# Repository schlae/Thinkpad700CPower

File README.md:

# Thinkpad 700C Power Supply Board

I've reverse engineered the power board from a Thinkpad 700C. The P/N is 35G4785, and the FRU number is 48G3712. A very similar or identical board is also present in the Thinkpad 700.

The schematic isn't perfect. Open a bug report if you find a mistake. Not all components were identified. A number of parts did not have designators on the silkscreen, so I assigned them new ones starting at 300.

The circuit board has four layers and an aluminum core, presumably for heat dissipation.

**Do not fabricate this design. The PCB layout is for reference only.** There are ground plane cuts in layer User.9 that need to get transferred to the ground plane. There are minor footprint differences as well. There are still unidentified components in the bill of materials.

## Disassembly

If you need information about disassembling a Thinkpad 700C to access the power board, refer to [my guide on iFixit](https://www.ifixit.com/Guide/IBM+Thinkpad+700C+Disassembly/173038).

## Troubleshooting

There is a single aluminum electrolytic capacitor on this board, C18 (47uF 6.3V) and, at least in my machine, it failed and leaked electrolyte everywhere. This is a problem because the electrolyte likes to puddle in nearby vias, and the acid in the solution etches away and can break the connection.

C43 and C19 are polymer electrolytic capacitors and are much more reliable than C18.

You can use the board layout to help with troubleshooting since it shows how the vias in this area should be connected.

## Operation

This is a very complicated design. I've added some notes to the schematic to hopefully make it easier to understand. Basically there is an input protection, power ORing circuit, and a set of four DC-DC converters. Two of them produce the main 5V rail--one of them from the tiny standby battery, the other from the battery+AC adapter. The remaining two generate two additional voltages. Several additional power rails are derived from these three but are gated by series-pass transistors, presumably for handling all the various power saving modes.

There is voltage monitoring for both overvoltage and undervoltage. Overvoltage causes a crowbar circuit to slam the AC adapter+battery voltage to zero. Undervoltage causes a power good output to deassert.

A pretty complicated circuit handles the power turn on and turn off, with many control lines coming from the motherboard.

Resistors with the "VR" prefix are laser-trimmed resistors on the circuit board itself. Using some sort of test fixture, the factory would measure critical voltage using a series of test points and make adjustments by firing a laser at these resistors.

# IBM Thinkpad Power Adapter 48G8942

I've also reverse engineered a compatible power adapter, FRU 48G8942. This is designed to output 10 to 20V at 2.20A or 3.38A.

## Design

The power adapter is a relatively straightforward design. IC051 is a primary-side switching power supply controller that produces 20VDC on the secondary side output. IC151 is a dual op-amp chip that regulates either voltage or current, as determined by D151. If the current is below the regulation limit, then the voltage control loop regulates the output voltage to 20V. If the current limit is reached, then the power supply lowers the voltage to limit the current.

There are two possible values for the current regulation, controlled by the state of the "INPUT SIGNAL" pin on the power plug.

* Floating or high: 2.2A
* Pulled low: 3.38A

The Thinkpad laptop pulls this pin low when it is operating, and allows it to float when it is powered off or in standby mode.

Unlike modern laptops, this early Thinkpad power supply also acts as the battery charger, so it tries to charge the batteries with a constant current. If the laptop is operating, it is also using current, so the charger has to increase the current to compensate and maintain the same charging current.

# Thinkpad 700 Series Battery 53G9510

This battery has a built-in LED fuel gauge and button. Pushing the button
causes the LEDs to light up, indicating the amount of charge left.

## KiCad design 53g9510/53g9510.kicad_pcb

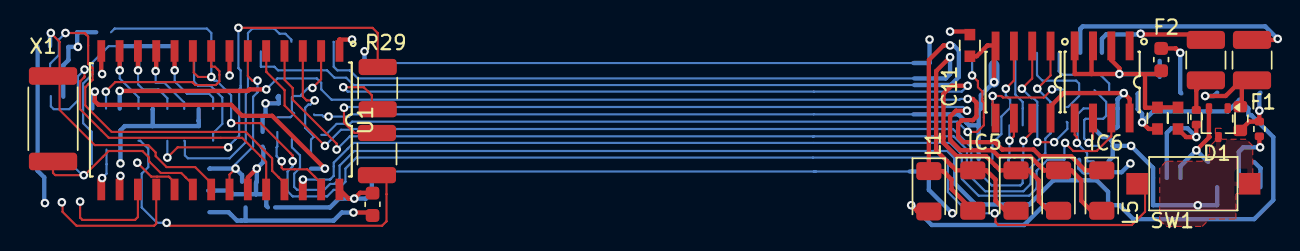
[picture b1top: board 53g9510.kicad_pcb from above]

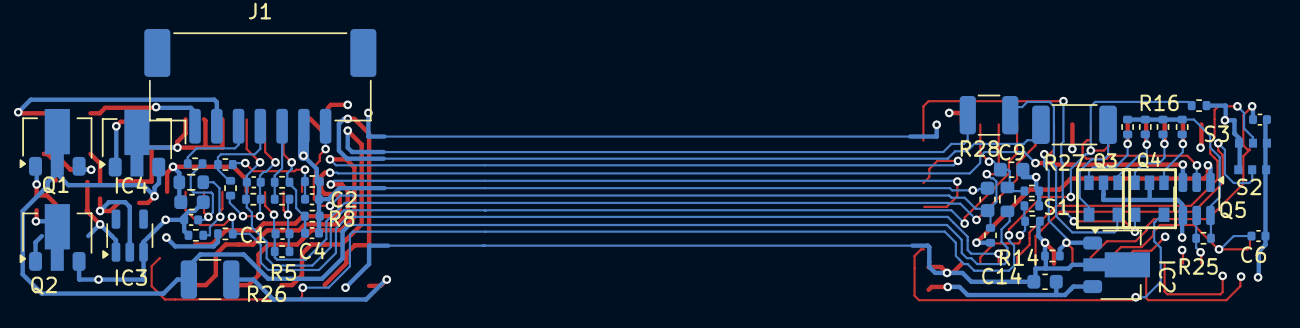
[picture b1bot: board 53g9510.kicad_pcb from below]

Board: 4 copper layers, 72 parts (49 on the bottom side), 49 nets.

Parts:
C1, C2, C4, C100, C102: 2.2nF; C_0402_1005Metric
C6, C106: 100pF; C_0402_1005Metric
C9, C14, C107, C108: 0.33uF; C_0603_1608Metric
C11, C104: 0.38uF; CAPC1608X100
C101: 0.36uF; C_0603_1608Metric
C103: 39nF; CAPC1608X100
C105: 2.6uF; C_0603_1608Metric
D1: 1SS300; SOT-323_SC-70
F1, F2: 1.0A; Fuse_1210_3225Metric
IC2: TC54VC3902MB; SOT-89-3
IC3: CEF (or EEF?); SOT-23-5
IC4: VREG; SOT-89-3
IC5: LM358; SOP127P620X175-8
IC6: LM393; SOP127P620X175-8
J1: Conn_01x07; JST_ZE_BM07B-ZESS-TBT_1x07-1MP_P1.50mm_Vertical
L1, L2, L3, L4, L5: LED_Small_Filled; LED_1206_3216Metric
Q1: 2SJ238; SOT-89-3
Q2: 2SK1717; SOT-89-3
Q3, Q4: "XE"; SOT23-5
Q5: "VF"; SOT-23-6
R5, R8, R14, R16, R100, R103, R109: 100.0K; R_0402_1005Metric
R25: 5.6K; R_0402_1005Metric
R26: 300; R_1210_3225Metric
R27: 330; R_2010_5025Metric
R28: 240; R_1210_3225Metric
R29: 160; R_1210_3225Metric
R101, R102, R104, R105: 2.00K; R_0402_1005Metric
R106: 10.00K; R_0402_1005Metric
R107: 160K; R_0603_1608Metric
R108: 20.00K; R_0402_1005Metric
R110: 100.0; R_0402_1005Metric
R111: 200K; R_0603_1608Metric
R112: 10.0K; R_0402_1005Metric
R113: 82; R_1210_3225Metric
R114, R115, R116, R117: 8.2K; R_0402_1005Metric
R118: 61.9K; R_0402_1005Metric
R119: 300K; R_0603_1608Metric
R120, R121: 100K; R_0402_1005Metric
S1: DNI; R_0402_1005Metric
S2, S3: Jumper_3_Open; JMP1005_3
SW1: SW_SPST; SW_SPST_CK_RS282G05A3
U1: TMP47C241; SOP127P1070X255-28
X1: 2MHz; R_2512_6332Metric

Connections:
+BATT: C103.2, IC4.3, Q1.2 (D), R26.1, R119.1
/BUT: R16.1, SW1.1 (A), U1.9 (R82/~INT1)
/Net1: L1.1 (K), L2.2 (A), R27.1
/Net2: L2.1 (K), L3.2 (A), R28.1
/Net3: L3.1 (K), L4.2 (A), R29.2
/Net4: L4.1 (K), L5.2 (A), R113.1
/Net5: L5.1 (K), Q5.3 (C1)
/Net6: C100.1, IC5.1, R103.1, U1.4 (R42/AIN2)
/Net7: C100.2, IC5.2 (-), R103.2, R104.1
/Net8: C4.1, IC5.3 (+), R8.1, R101.2
/Net9: C2.1, IC5.5 (+), R100.1, R105.2
/Net10: C1.2, IC5.6 (-), R5.2, R102.2
/Net11: C1.1, IC5.7, R5.1, U1.5 (R43/AIN3)
/Net12: J1.5, R101.1, R102.1
/Net13: J1.4, R104.2, R105.1
/Net14: J1.3, R106.1
/Net15: C102.2, IC6.6 (-), R106.2
/Net16: IC6.5 (+), R107.2, R108.2
/Net17: IC6.7, R109.2, U1.26 (K02)
/Net18: C107.1, J1.7, R118.2, U1.3 (R41/AIN1)
/Net20: L1.2 (A), R26.2
/Net21: F2.2, R110.1
/Net22: F1.1, Q1.3 (S), R111.1
/Net23: F1.2, J1.2
/Net24: F2.1, J1.1
/Net25: C104.2, IC3.2, R110.2
/Net26: D1.2 (K), IC3.1, Q2.1 (G)
/Net27: Q2.2 (D), R112.2
/Net28: Q1.1 (G), R111.2, R112.1
/Net29: Q3.5 (C1), R28.2
/Net30: Q3.4 (C2), R27.2
/Net31: Q4.5 (C1), R113.2
/Net32: Q4.4 (C2), R29.1
/Net33: Q3.1 (B1), R115.2, U1.11
/Net34: Q4.3 (B2), R116.2, U1.12
/Net35: Q4.1 (B1), R117.2, U1.13
/Net36: Q5.5 (B1), R25.2, U1.15 (P20)
/Net37: R121.1, S1.1, U1.27 (K03)
/Net38: C9.1, R119.2, R120.1, U1.2 (R40/AIN0)
/Net39: Q5.6 (C1), R25.1, R114.1, R115.1, R116.1, R117.1
/Net40: Q5.2 (B1), U1.8 (R81/T2)
/Net41: Q3.3 (B2), R114.2, U1.10
/S2: S2.2 (C), U1.24 (K00)
/S3: S3.2 (C), U1.25 (K01)
/XIN: C6.1, U1.20 (XIN), X1.1
/~RST: IC2.1 (~RST), R14.2, U1.6 (R71/~WTO), U1.22 (~RESET)
GND: C2.2, C4.2, C6.2, C9.2, C11.1, C14.2, C101.2, C102.1, C103.1, C104.1, C105.2, C106.2, C107.2, C108.2, D1.3 (A), IC2.3 (VSS), IC3.3, IC4.2, IC5.4 (V-), IC6.2 (-), IC6.3 (+), IC6.4 (V-), J1.6, Q2.3 (S), Q3.2 (E), Q4.2 (E), Q5.4 (E1), R8.2, R100.2, R108.1, R120.2, S1.2, S2.3 (B), S3.3 (B), SW1.2 (B), U1.14 (VSS), U1.19 (TEST)
unnamed: C106.1, U1.21 (XOUT), X1.2
VCC: C11.2, C14.1, C101.1, C105.1, C108.1, IC2.2 (VDD), IC4.1, IC5.8 (V+), IC6.8 (V+), Q5.1 (E1), R14.1, R16.2, R107.1, R109.1, R118.1, R121.2, S2.1 (A), S3.1 (A), U1.1 (VAREF), U1.7 (R80/~INT2), U1.23 (~HOLE/~KE0), U1.28 (VDD)

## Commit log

2023-04-15 update voltage rail names
2023-05-06 Add power brick schematic
2023-05-27 Add docking connector and HDD connector pinouts
2023-06-07 Minor updates to dock pinout
2023-06-16 Moving the docking pinout description
2023-11-02 Add reverse engineered board layout.
2023-11-02 Some component value updates
2023-11-11 Added 700 no-pop positions
2024-05-22 Add link to disassembly instructions
2024-05-22 Set active layers to better default
2025-05-12 Add 53G9510 battery
2025-05-12 Add info on external battery current sense
2025-05-12 Add flex circuit to 53g9510
